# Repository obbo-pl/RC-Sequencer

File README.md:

# RC-Sequencer
  The purpose of the system is to switch on several electrical circuits using one RC channel. The change of state takes place according to programmed sequences. 

##### Main features:
- 4 output circuits,
- 8 programmed sequences,
- sequence selection by jumper configuration,
- maximum length of programmed sequence 15 (ATtiny24), 31 (ATtiny44), 63 (ATtiny84),
- the ability to change the sequence in both directions,
- maximum output circuit current: 1A,
- maximum voltage for output circuits: 20V.

### Hardware & Firmware.
These sections covers info on building sample hardware, including schematics, PCBs, and the corresponding firmware.

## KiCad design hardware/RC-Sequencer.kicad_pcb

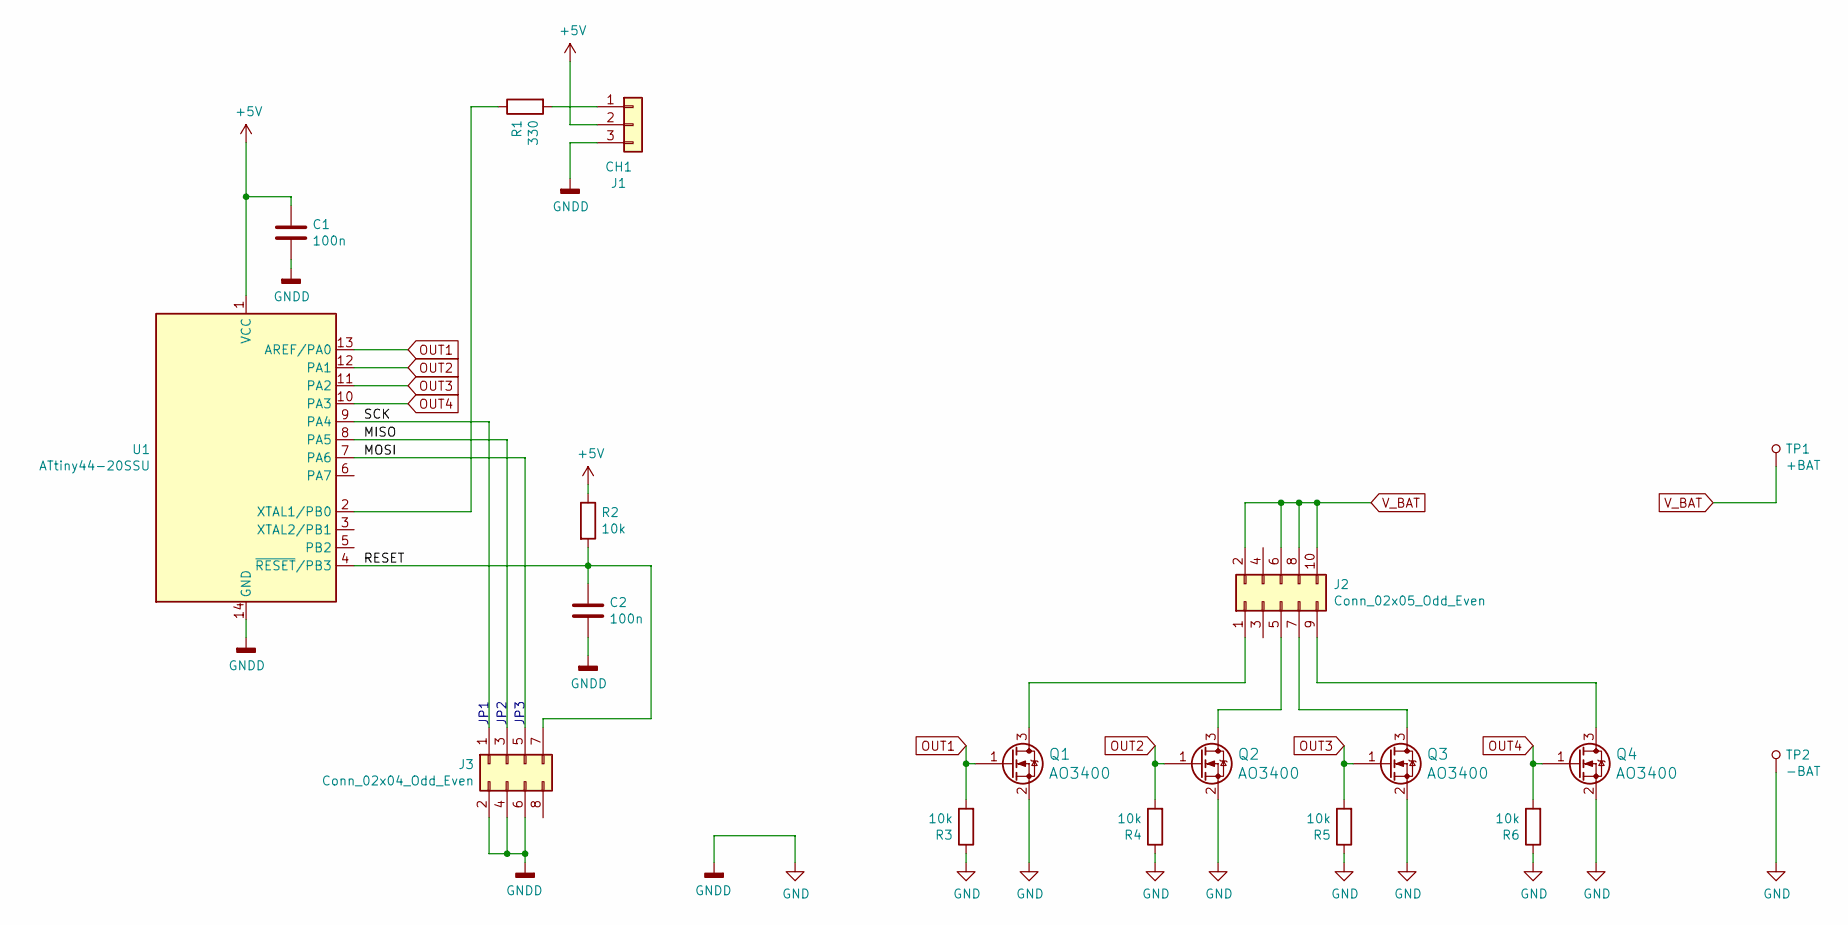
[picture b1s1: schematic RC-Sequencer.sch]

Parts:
C1, C2: 100n; C_0805K
J1: CH1; PinHeader_1x03_P2.54mm_Horizontal_PAD_noPinSilk
J2: Conn_02x05_Odd_Even; PinHead_2x05_P2.54mm_SMD_Horizontal_Edge
J3: Conn_02x04_Odd_Even; PinHead_2x04_P2.54mm_SMD_Horizontal_Edge
Q1, Q2, Q3, Q4: AO3400; SOT-23_HandSoldering
R1: 330; R_0805K
R2, R3, R4, R5, R6: 10k; R_0805K
TP1: +BAT; SolderWirePad_single_SMD_3x8mm
TP2: -BAT; SolderWirePad_single_SMD_3x8mm
U1: ATtiny44-20SSU; SOIC-14_3.9x8.7mm_P1.27mm

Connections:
+5V: C1.1, J1.2, R2.1, U1.1 (VCC)
/MISO: J3.3, U1.8 (PA5)
/MOSI: J3.5, U1.7 (PA6)
/RESET: C2.1, J3.7, R2.2, U1.4 (~RESET~/PB3)
/SCK: J3.1, U1.9 (PA4)
GND: C1.2, C2.2, J1.3, J3.2, J3.4, J3.6, Q1.2 (S), Q2.2 (S), Q3.2 (S), Q4.2 (S), R3.1, R4.1, R5.1, R6.1, TP2.1, U1.14 (GND)
unnamed: J1.1, R1.2
unnamed: J2.1, Q1.3 (D)
unnamed: J2.5, Q2.3 (D)
unnamed: J2.7, Q3.3 (D)
unnamed: J2.9, Q4.3 (D)
unnamed: R1.1, U1.2 (XTAL1/PB0)
OUT1: Q1.1 (G), R3.2, U1.13 (AREF/PA0)
OUT2: Q2.1 (G), R4.2, U1.12 (PA1)
OUT3: Q3.1 (G), R5.2, U1.11 (PA2)
OUT4: Q4.1 (G), R6.2, U1.10 (PA3)
V_BAT: J2.2, J2.6, J2.8, J2.10, TP1.1

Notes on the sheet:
JP1
JP2
JP3

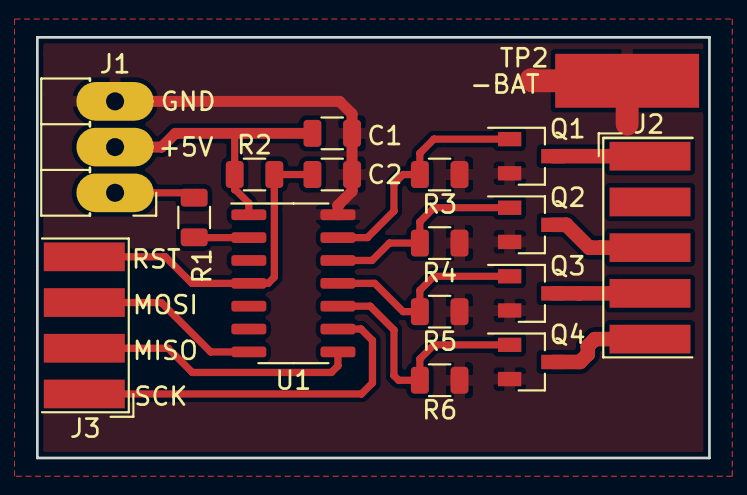
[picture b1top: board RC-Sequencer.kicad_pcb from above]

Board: 2 copper layers, 37.3 x 23.4 mm, 18 parts (1 on the bottom side), 17 nets.
